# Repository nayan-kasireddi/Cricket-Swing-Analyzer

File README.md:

# Crease: Cricket Swing Analyzer

**Embedded Systems | Raspberry Pi Pico 2 W | MPU6050 | Arduino | Web | Python | KiCad**

**Live site: [creasecricketswing.netlify.app](https://creasecricketswing.netlify.app)**

A sensor on a cricket bat, and a website that turns its motion into swings you can see. A Raspberry Pi Pico 2 W reads an MPU6050 motion sensor 500 times a second. Plug it into your computer, open Crease in the browser, and watch each swing appear as you practice.

## What it does

- **Reads the sensor:** the firmware samples 3-axis acceleration and 3-axis rotation at a **500 Hz** target (±16 g, ±2000 deg/s) and streams them over USB.
- **Shows your practice live:** the Crease website connects to the sensor from the browser, draws your swing as it happens, and counts each swing.
- **Reviews every session:** a session chart with the detected swings shaded, a scorecard for each swing, and a summary you can download.
- **Works without a sensor:** a demo mode lets anyone try the site with sample data.
- **Keeps your data private:** your readings stay in your browser.

## Try it

1. Open **[creasecricketswing.netlify.app](https://creasecricketswing.netlify.app)**.
2. Click **Try a demo** to see how it works with sample data, no hardware needed.
3. To use the real sensor, plug the Pico into your computer with a data USB cable and click **Connect sensor**. Live sensor access works in **desktop Chrome and Edge**, and the browser remembers the sensor for next time.
4. Move the sensor. Each swing is counted and added to the scorecard. Use the **swing trigger** slider (2.5 g by default) to make detection more or less sensitive.

### What the numbers mean

| Reading | Meaning |
|---|---|
| Swings detected | How many swings the trigger picked out |
| Peak acceleration | The strongest push on the sensor, in g, including gravity (a sensor lying still reads about 1 g) |
| Peak rotation | How fast the bat turns, in degrees per second (360 deg/s is one full turn a second) |
| Last swing | How long the swing lasted, in seconds |

**About bat speed:** the sensor records acceleration and rotation, not the speed of the bat head in km/h. Crease does not estimate bat speed or compare you with named players, because that needs a validated bat-speed sensor and comparable published measurements. Detected swings are a practice aid, so tune the trigger for your sensor and movement.

## How it works

```text
 Pico 2 W (C++ firmware)                       Your computer
 ─────────────────────────                     ─────────────────────────────────────
 MPU6050 over I²C, every 2 ms
 prints one CSV line per sample ── USB ──►    Crease website (desktop Chrome or Edge)
                                               reads the sensor, finds the swings,
                                               and draws your session
```

The firmware and the website never call each other. They only agree on the text format of each line (see [Data format](#data-format)).

## Using the real sensor

1. **Wire the sensor** (see [Hardware](#hardware)) and **upload the firmware** `firmware/pico2w_mpu6050/pico2w_mpu6050.ino` with the Arduino IDE and the Arduino-Pico board package. Hold **BOOTSEL** while plugging the Pico in for the first upload.
2. **Plug the Pico into your computer** with a data USB cable. Close the Arduino Serial Monitor first, because it locks the port.
3. Open the site, click **Connect sensor**, and choose the Pico from the list.

If the Pico loses power or a wire comes loose while running, replug the Pico so the firmware sets the sensor up again.

## Hardware

| Component | Purpose |
|---|---|
| Raspberry Pi Pico 2 W | Main microcontroller |
| MPU6050 (GY-521) | 6-axis accelerometer and gyroscope |
| Breadboard and jumper wires | Prototyping |
| USB cable (data-capable) | Power, programming and serial data |
| Custom PCB (in progress) | Compact version for mounting on a bat |

| MPU6050 | Raspberry Pi Pico 2 W |
|---|---|
| VCC | 3V3 (Pin 36) |
| GND | GND (Pin 38) |
| SDA | GP4 (Pin 6) |
| SCL | GP5 (Pin 7) |

The sensor communicates over I²C at address `0x68`.

## Firmware

**Location:** `firmware/pico2w_mpu6050/pico2w_mpu6050.ino` (C++, Arduino)

- Configures the MPU6050 for ±16 g and ±2000 deg/s, and checks the sensor configuration at start-up
- Reads the sensor over I²C at 400 kHz and converts raw values to g and deg/s
- Polls on a fixed 2000 µs schedule (a 500 Hz target) and counts any missed slots in `skipped_slots`
- Streams one line per sample at 115200 baud, with start-up and error diagnostics as `#` comment lines

The other sketches in `firmware/` are earlier bring-up tests (LED and button checks).

## Data format

Each line the firmware sends:

```csv
time_us,ax_g,ay_g,az_g,gx_dps,gy_dps,gz_dps,skipped_slots
94754100,0.1135,-0.0537,1.0270,-0.55,1.69,0.78,0
```

| Field | Description | Unit |
|---|---|---|
| time_us | Time since the board powered on | Microseconds |
| ax_g, ay_g, az_g | Acceleration along X, Y, Z | g |
| gx_dps, gy_dps, gz_dps | Rotation around X, Y, Z | Degrees/second |
| skipped_slots | Sample slots missed so far | Count |

Lines starting with `#` (a startup banner and sensor error notes) are not data. A 500 Hz target is not a guarantee that every sample arrives on time, so check `skipped_slots` and the sample rate in recordings.

## Python tools

The `python/` folder holds the analysis code used to build and test the project, and it still works on its own for offline checks of recordings.

| File | What it does |
|---|---|
| `python/ingest.py` | `load_csv()`: loads a recording, converts units, and checks it (columns, 500 Hz rate, gaps, increasing timestamps, plausible ranges) |
| `python/swings.py` | `SwingTracker`, `detect_swings()`, `summarize_swings()` |
| `python/analyze.py` | Acceleration and rotation magnitude, static plots from the command line |
| `python/live.py` | Reads the serial port, saves a CSV, and logs swings |
| `python/generate_test_data.py` | Makes synthetic recordings (stationary, slow, normal and multi-swing) |
| `python/dashboard.py`, `python/ui.py` | An earlier Streamlit dashboard, kept for reference |
| `python/core.py` | Placeholder for an alternative analysis implementation, not used |
| `python/tests/` | Automated tests |

```bash
git clone https://github.com/nayan-kasireddi/Cricket-Swing-Analyzer.git
cd Cricket-Swing-Analyzer
python -m venv .venv
source .venv/bin/activate          # Windows: .venv\Scripts\activate
pip install -r requirements.txt

python -m pytest -q                       # run the automated tests
python -m python.live --sim               # live graph with a fake sensor
python -m python.analyze data/synthetic/multi_swing.csv   # static plots from a recording
```

Developed on Python 3.14, and Python 3.12 has also been validated. Package versions are not pinned in `requirements.txt`, so a newer release of a library could behave differently.

### Why one swing counts once

A bat swing is one smooth sweep of rotation, but the acceleration has several spikes inside it: the hands speeding the bat up, a peak around contact, and the sudden stop in the follow-through, with dips in between. Counting every spike would count one swing three times.

The Python `SwingTracker` treats a swing as active while the force is high **or** the bat is still rotating faster than 150 deg/s. It ends the swing only after things stay calm for 0.2 s, and then ignores new swings for 1 s (a batter cannot swing again that fast).

## Current status and limits

This is a working prototype, and it has not yet seen real bat swings.

- **Tuned on synthetic data and hand movements.** The swing trigger and the other detection settings are provisional. They need retuning on recordings from a sensor mounted on a bat.
- **No bat speed, impact, or force in newtons.** The sensor measures acceleration and rotation only, and Crease reports exactly that.
- **Sensor range:** at ±16 g and ±2000 deg/s, a hard hit with the sensor far from the hands could exceed the accelerometer's range.
- **Browser support:** live sensor access needs desktop Chrome or Edge. Other browsers and phones can use the demo.
- **Not built yet:** impact (bat-ball contact) detection, swing-type classification, and wireless transmission. These need real swing data first.

## Development progress

| Milestone | Status |
|---|---|
| Repository setup and documentation | Complete |
| Pico 2 W firmware upload and LED testing | Complete |
| MPU6050 wiring and soldering | Complete |
| I²C sensor detection | Complete |
| Accelerometer and gyroscope streaming | Complete |
| 500 Hz firmware implementation | Complete |
| CSV loading and data validation | Complete |
| Swing detection (counted once per swing) | Complete |
| Crease website: live practice and session review | Complete |
| Automated tests (40+) | Complete |
| Controlled swing data collection on a bat | Upcoming |
| Threshold tuning on real swings | Upcoming |
| Impact detection | Planned |
| Swing-type classification | Planned |
| KiCad schematic and PCB layout | In progress |
| PCB fabrication and assembly | Planned |
| Final demonstration | Planned |

See [`docs/devlog.md`](docs/devlog.md) and [`docs/shayon_chakraborti_devlog.md`](docs/shayon_chakraborti_devlog.md) for detailed updates.

## Troubleshooting

| Issue | Suggested solution |
|---|---|
| Connect sensor does nothing, or the sensor is not listed | Use desktop Chrome or Edge, a data-capable USB cable, and replug the Pico |
| "Port busy" or cannot open the port | Close the Arduino Serial Monitor or any other program using the sensor |
| Readings stop or look wrong after a loose wire | Unplug and replug the Pico so the firmware sets the sensor up again |
| Too many or too few swings | Adjust the swing trigger slider |
| MPU6050 not detected | Check wiring, solder joints, and I²C address `0x68` |
| Firmware upload fails | Hold BOOTSEL while plugging in the Pico, and confirm the board selection |

## Authors

Crease was developed by both authors.

**Nayan Kasireddi** — hardware, firmware, and PCB design
Electrical and Computer Engineering, The University of Texas at Austin
GitHub: [@nayan-kasireddi](https://github.com/nayan-kasireddi)

**Shayon Chakraborti** — Python data pipeline, swing detection, and testing
Statistics and Data Science, The University of Texas at Austin
GitHub: [@Shayon2307](https://github.com/Shayon2307)

## Acknowledgments

Built with the Raspberry Pi Pico platform, the MPU6050 motion sensor, Arduino, Python (NumPy, pandas, Matplotlib, pySerial), and KiCad. Hardware prototyping and fabrication resources are available through Texas Inventionworks at The University of Texas at Austin.

## Project resources

- [Crease website](https://creasecricketswing.netlify.app)
- [GitHub repository](https://github.com/nayan-kasireddi/Cricket-Swing-Analyzer)
- [Firmware](firmware/pico2w_mpu6050/pico2w_mpu6050.ino)
- [Development logs](docs/)
- [Python code](python/)

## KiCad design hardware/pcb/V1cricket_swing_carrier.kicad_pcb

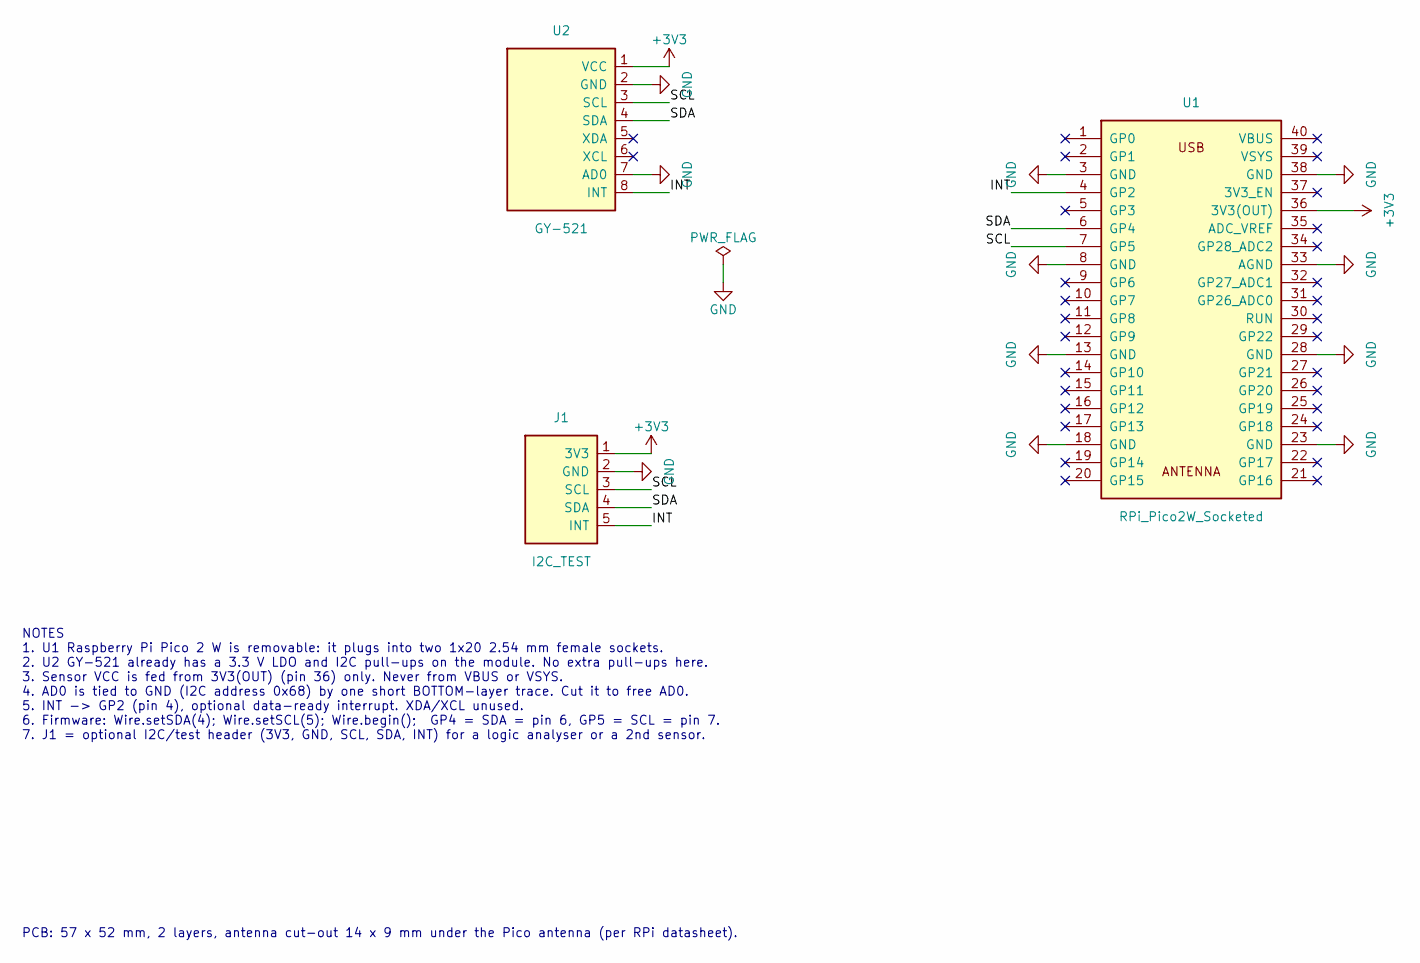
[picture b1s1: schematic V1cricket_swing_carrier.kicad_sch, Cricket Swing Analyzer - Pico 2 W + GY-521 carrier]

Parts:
J1: I2C_TEST; PinHeader_1x05_P2.54mm_Vertical
U1: RPi_Pico2W_Socketed
U2: GY-521; GY-521_HW-123_1x08

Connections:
+3V3: J1.1 (3V3), U1.36 (3V3(OUT)), U2.1 (VCC)
/INT: J1.5 (INT), U1.4 (GP2), U2.8 (INT)
/SCL: J1.3 (SCL), U1.7 (GP5), U2.3 (SCL)
/SDA: J1.4 (SDA), U1.6 (GP4), U2.4 (SDA)
GND: J1.2 (GND), U1.3 (GND), U1.8 (GND), U1.13 (GND), U1.18 (GND), U1.23 (GND), U1.28 (GND), U1.33 (AGND), U1.38 (GND), U2.2 (GND), U2.7 (AD0)

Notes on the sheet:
NOTES 1. U1 Raspberry Pi Pico 2 W is removable: it plugs into two 1x20 2.54 mm female sockets. 2. U2 GY-521 already has a 3.3 V LDO and I2C pull-ups on the module. No extra pull-ups here. 3. Sensor VCC is fed from 3V3(OUT) (pin 36) only. Never from VBUS or VSYS. 4. AD0 is tied to GND (I2C address 0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
PCB: 57 x 52 mm, 2 layers, antenna cut-out 14 x 9 mm under the Pico antenna (per RPi datasheet).

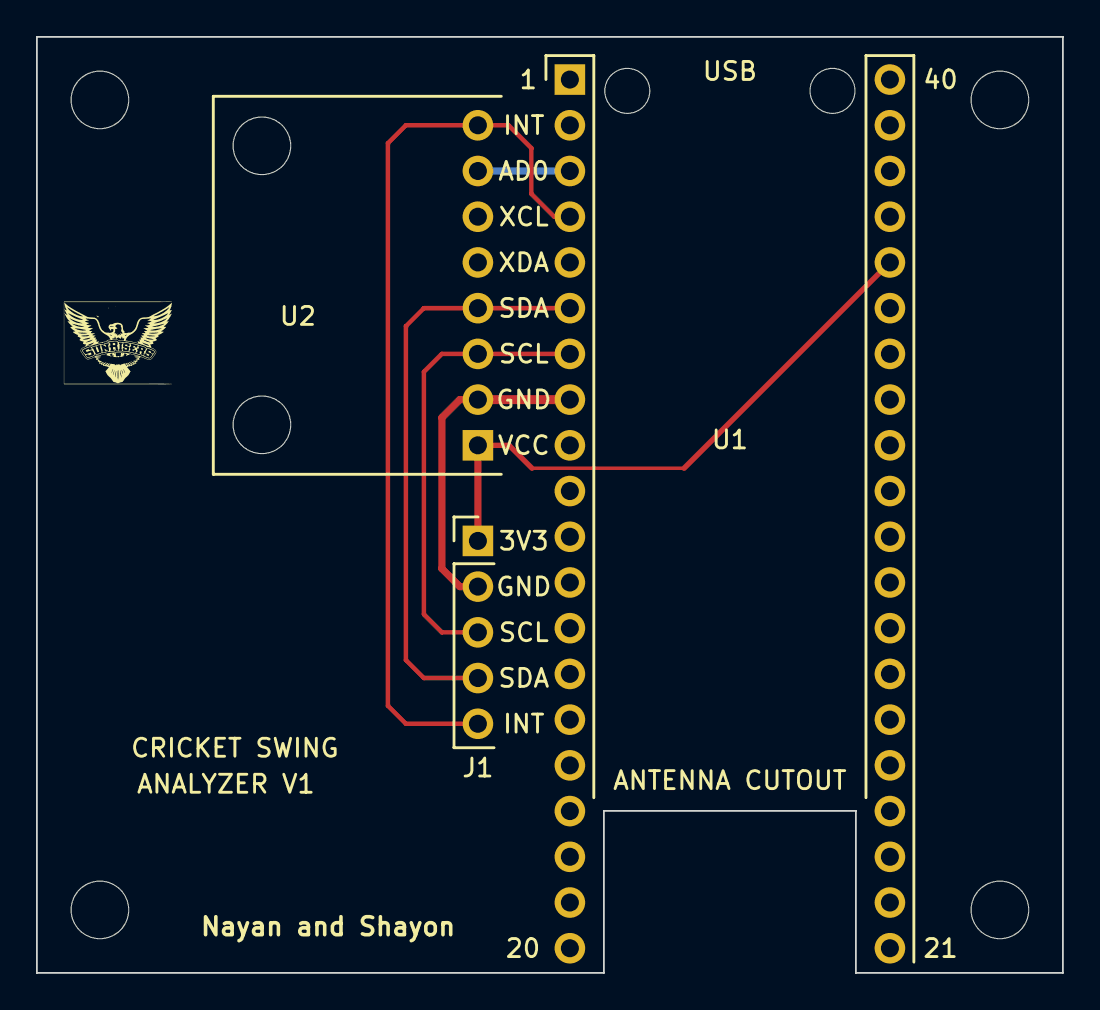
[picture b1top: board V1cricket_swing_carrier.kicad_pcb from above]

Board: 2 copper layers, 57.0 x 52.0 mm, 7 parts (0 on the bottom side), 5 nets.

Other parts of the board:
H1, H2, H3, H4: MountingHole_3.2mm_M3
